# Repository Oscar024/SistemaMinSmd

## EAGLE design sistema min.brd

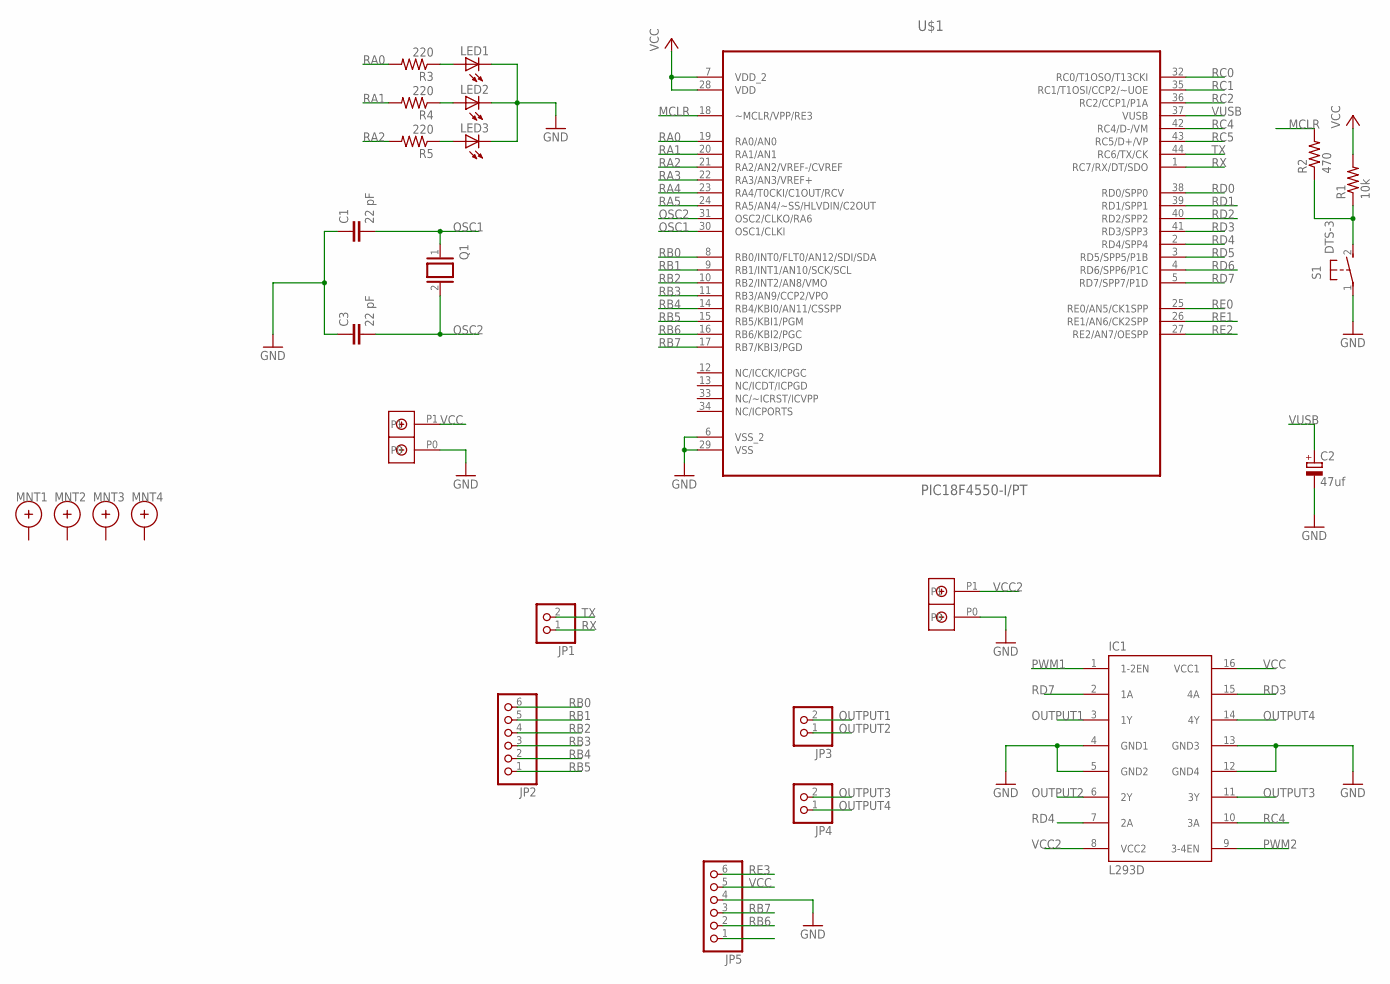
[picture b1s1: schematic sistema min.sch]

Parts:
C1, C3: 22 pF; C1206
C2: 47uf; 153CLV-0605
IC1: L293D; DIL16
JP1, JP3, JP4: PINHD-1X2; 1X02
JP2, JP5: PINHD-1X6; 1X06
LED1, LED2, LED3: LEDCHIPLED_1206; CHIPLED_1206
MNT1, MNT2, MNT3, MNT4: HOLE_MNT_0.135; HOLE_MNT_#5-40
Q1: XTAL/S; QS
R1: 10k; M1206
R2: 470; M1206
R3, R4, R5: 220; M1206
S1: DTS-3
U$1: PIC18F4550-I/PT; QFP80P1200X1200X120-44N
U$2, U$3: DBCONN-1X2

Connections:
GND: C1.1, C2.-, C3.1, IC1.4 (GND1), IC1.5 (GND2), IC1.12 (GND4), IC1.13 (GND3), JP5.4, LED1.C, LED2.C, LED3.C, S1.1, U$1.6 (VSS_2), U$1.29 (VSS), U$2.P0, U$3.P0
MCLR: R2.2, U$1.18 (~MCLR/VPP/RE3)
unnamed: R1.1, R2.1, S1.2
unnamed: LED1.A, R3.1
unnamed: LED2.A, R4.1
unnamed: LED3.A, R5.1
OSC1: C1.2, Q1.1, U$1.30 (OSC1/CLKI)
OSC2: C3.2, Q1.2, U$1.31 (OSC2/CLKO/RA6)
OUTPUT1: IC1.3 (1Y), JP3.2
OUTPUT2: IC1.6 (2Y), JP3.1
OUTPUT3: IC1.11 (3Y), JP4.2
OUTPUT4: IC1.14 (4Y), JP4.1
PWM1: IC1.1 (1-2EN)
PWM2: IC1.9 (3-4EN)
RA0: R3.2, U$1.19 (RA0/AN0)
RA1: R4.2, U$1.20 (RA1/AN1)
RA2: R5.2, U$1.21 (RA2/AN2/VREF-/CVREF)
RA3: U$1.22 (RA3/AN3/VREF+)
RA4: U$1.23 (RA4/T0CKI/C1OUT/RCV)
RA5: U$1.24 (RA5/AN4/~SS/HLVDIN/C2OUT)
RB0: JP2.6, U$1.8 (RB0/INT0/FLT0/AN12/SDI/SDA)
RB1: JP2.5, U$1.9 (RB1/INT1/AN10/SCK/SCL)
RB2: JP2.4, U$1.10 (RB2/INT2/AN8/VMO)
RB3: JP2.3, U$1.11 (RB3/AN9/CCP2/VPO)
RB4: JP2.2, U$1.14 (RB4/KBI0/AN11/CSSPP)
RB5: JP2.1, U$1.15 (RB5/KBI1/PGM)
RB6: JP5.2, U$1.16 (RB6/KBI2/PGC)
RB7: JP5.3, U$1.17 (RB7/KBI3/PGD)
RC0: U$1.32 (RC0/T1OSO/T13CKI)
RC1: U$1.35 (RC1/T1OSI/CCP2/~UOE)
RC2: U$1.36 (RC2/CCP1/P1A)
RC4: IC1.10 (3A), U$1.42 (RC4/D-/VM)
RC5: U$1.43 (RC5/D+/VP)
RD0: U$1.38 (RD0/SPP0)
RD1: U$1.39 (RD1/SPP1)
RD2: U$1.40 (RD2/SPP2)
RD3: IC1.15 (4A), U$1.41 (RD3/SPP3)
RD4: IC1.7 (2A), U$1.2 (RD4/SPP4)
RD5: U$1.3 (RD5/SPP5/P1B)
RD6: U$1.4 (RD6/SPP6/P1C)
RD7: IC1.2 (1A), U$1.5 (RD7/SPP7/P1D)
RE0: U$1.25 (RE0/AN5/CK1SPP)
RE1: U$1.26 (RE1/AN6/CK2SPP)
RE2: U$1.27 (RE2/AN7/OESPP)
RE3: JP5.6
RX: JP1.1, U$1.1 (RC7/RX/DT/SDO)
TX: JP1.2, U$1.44 (RC6/TX/CK)
VCC: IC1.16 (VCC1), JP5.5, R1.2, U$1.7 (VDD_2), U$1.28 (VDD), U$2.P1
VCC2: IC1.8 (VCC2), U$3.P1
VUSB: C2.+, U$1.37 (VUSB)

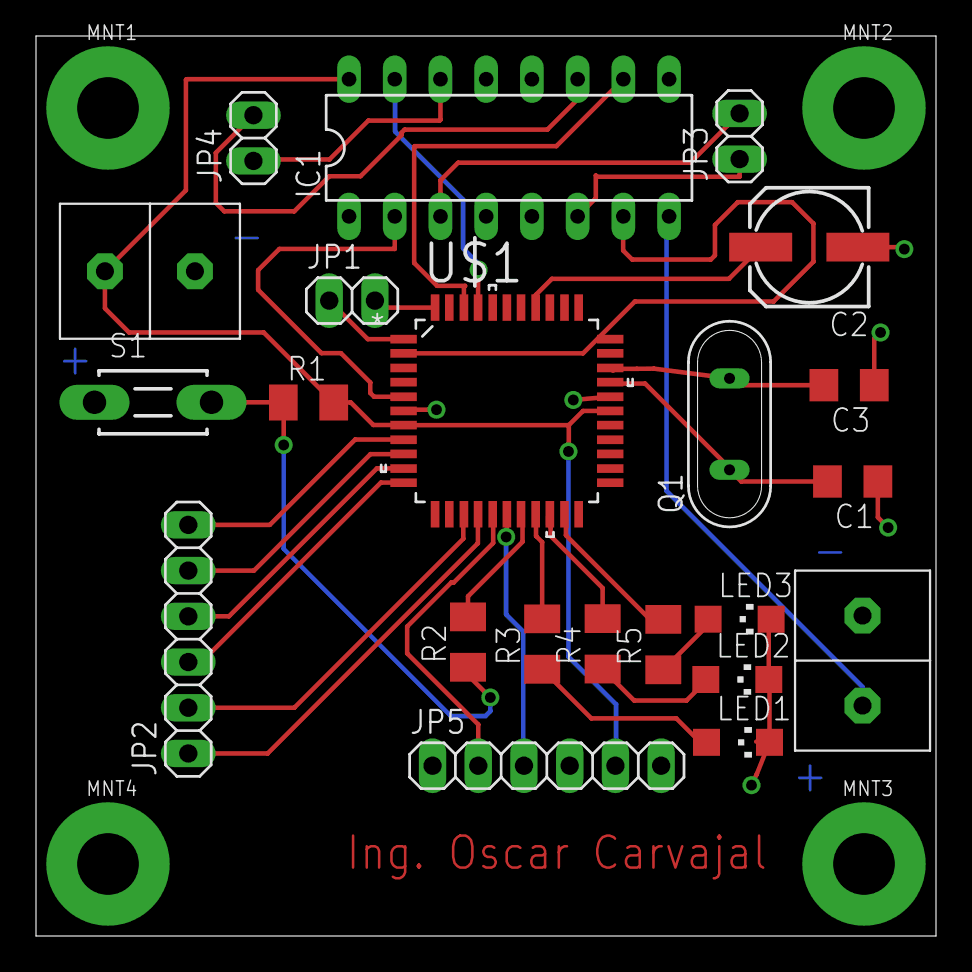
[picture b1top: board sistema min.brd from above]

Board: 2 copper layers, 50.0 x 50.0 mm, 26 parts (0 on the bottom side), 32 nets.
